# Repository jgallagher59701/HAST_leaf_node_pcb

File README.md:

# HAST leaf node pcb files

The first PCB used EagleCAD, but I've switched to KiCAD. Version 0.5 is the current version of the PCB in used as of Nov. 2021.

Supportted by a grant from ESIP.

Contact: jgallagher@opendap.org

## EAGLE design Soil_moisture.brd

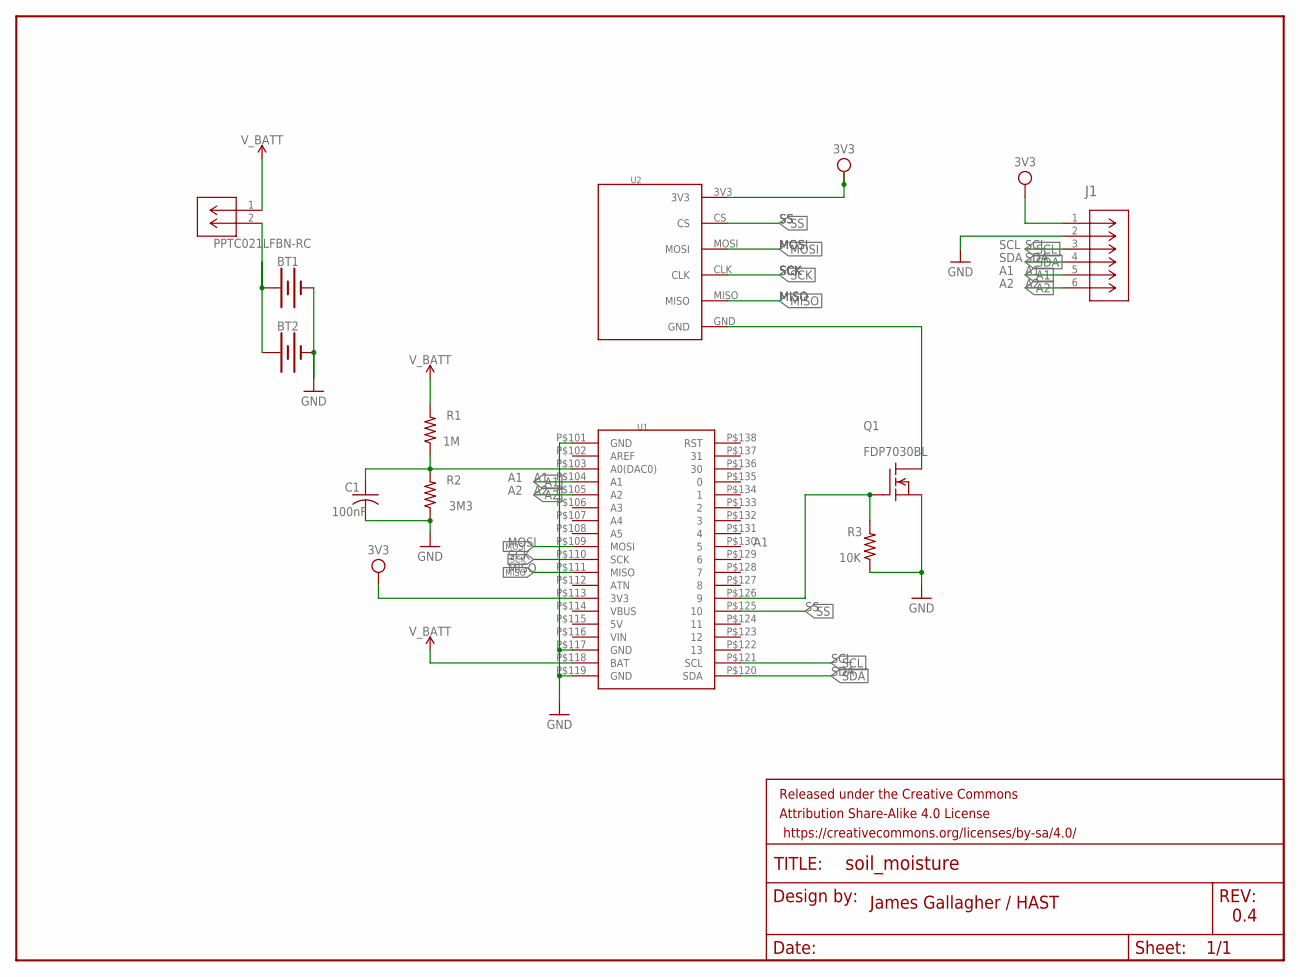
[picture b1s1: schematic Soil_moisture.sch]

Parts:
BAT_GND: PPTC021LFBN-RC; CONN2_LFBN-RC_SUL
BT1, BT2: BATTERY-AA_KIT; BATTERY-AA-KIT
C1: 100nF; C050-035X075
FRAME1: FRAME-LETTER; CREATIVE_COMMONS
J1: 1725698; CONN_1725698_PXC
Q1: FDP7030BL; TO220
R1: 1M; 0309/10
R2: 3M3; 0309/10
R3: 10K; 0309/10
U1: RS_MINI_ULTRA_PRO_V2
U2: SD_BREAKOUT_EBAY

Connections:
3V3: U1.P$113 (3V3)
A1: J1.5, U1.P$104 (A1)
A2: J1.6, U1.P$105 (A2)
GND: BT1.GND@1 (-), BT2.GND@1 (-), C1.2, J1.2, Q1.3 (S), R2.1, R3.1, U1.P$101 (GND), U1.P$117 (GND), U1.P$119 (GND)
MISO: U1.P$111 (MISO), U2.MISO
MOSI: U1.P$109 (MOSI), U2.MOSI
unnamed: Q1.2 (D), U2.GND
unnamed: C1.1, R1.1, R2.2, U1.P$103 (A0(DAC0))
unnamed: Q1.1 (G), R3.2, U1.P$126 (9)
unnamed: BAT_GND.2, BT1.PWR@1 (+), BT2.PWR@1 (+)
SCK: U1.P$110 (SCK), U2.CLK
SCL: J1.3, U1.P$121 (SCL)
SDA: J1.4, U1.P$120 (SDA)
SS: U1.P$125 (10), U2.CS
VCC: J1.1, U2.3V3
VIN: U1.P$116 (VIN)
V_BATT: BAT_GND.1, R1.2, U1.P$118 (BAT)

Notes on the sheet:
James Gallagher / HAST
0.4

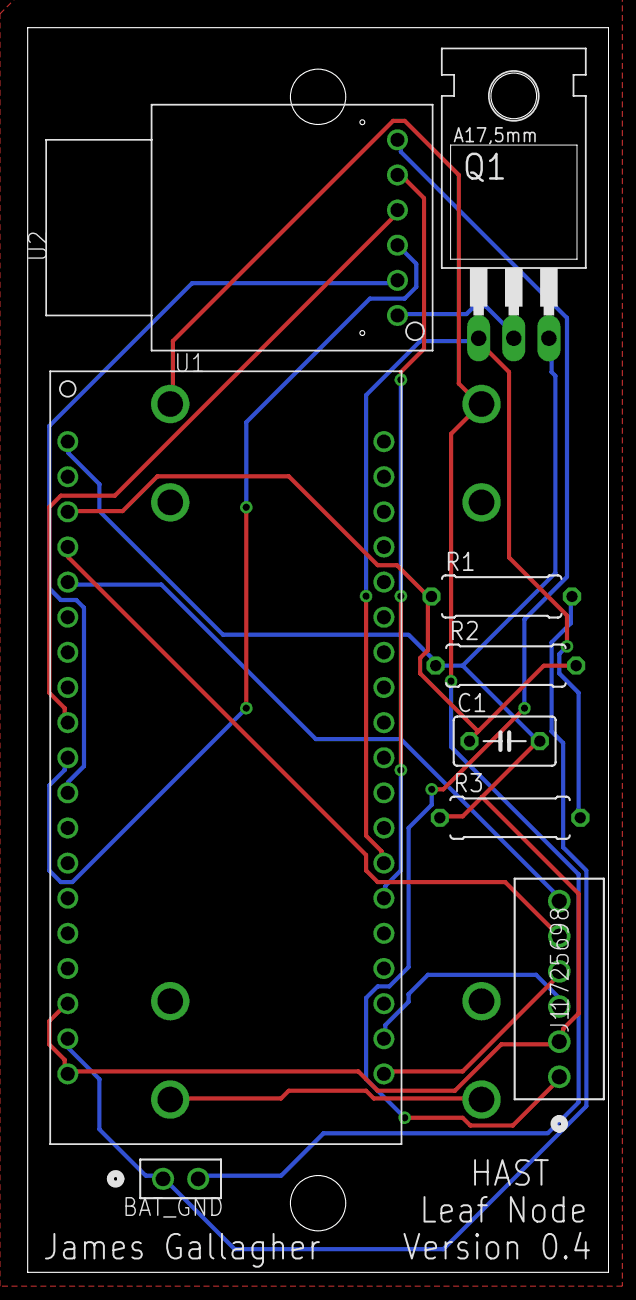
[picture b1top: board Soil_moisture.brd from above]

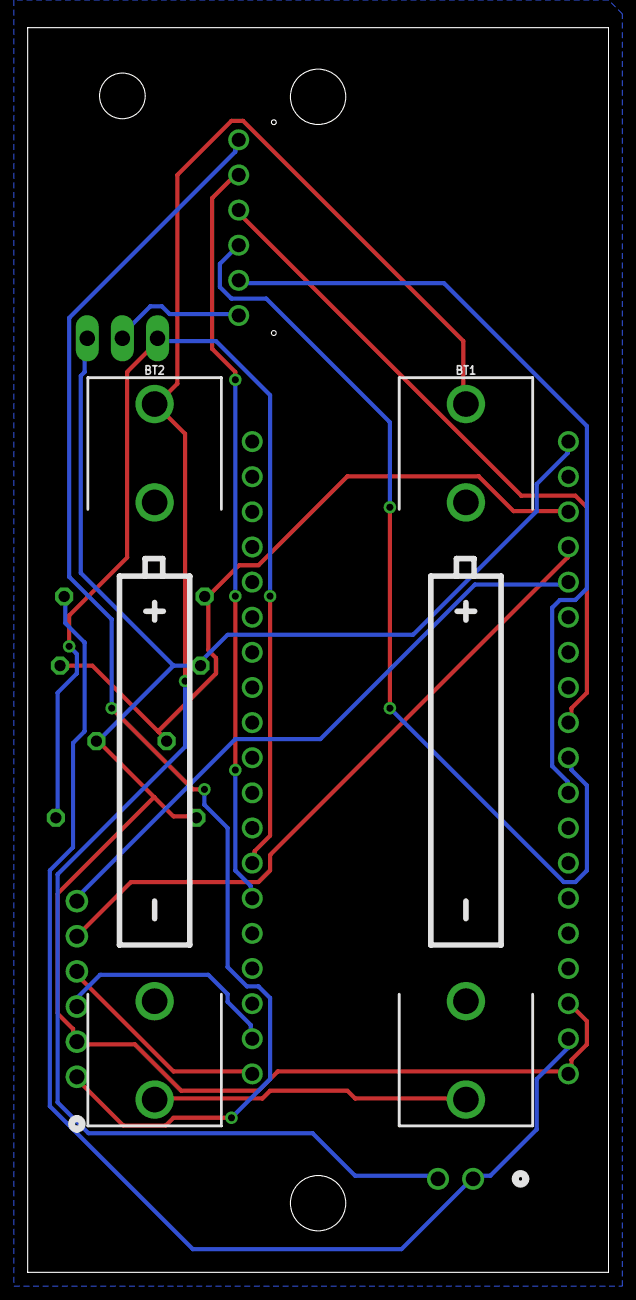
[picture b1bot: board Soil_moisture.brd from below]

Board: 2 copper layers, 42.0 x 90.0 mm, 12 parts (2 on the bottom side), 15 nets.

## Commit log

2021-03-10 Imported Eagle schematic to KiCAD, added the result here.
2021-03-10 Added a note about KiCAD 5 to the README
2021-08-27 PCB version 0.5 - now with 3D models
2021-08-28 Various hacks - added jumpers for GPIO/A0
2021-09-07 Added second voltage divider for Vbat; board outline
2021-09-09 Added Gerbers and a BOM
2021-09-13 BOM updates
2021-10-01 Added a PDF of the schematic
2021-10-01 At the office, KiCAD is using newer libraries.
    This is an update based on those newer libraries. I may
    have to update KiCAD at home to use the files on this branch.
    Test, merge if possible.
2021-11-18 Cache update
    Not sure this should be in git, but it is...

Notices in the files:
parts and their libraries:
SparkFun-Batteries: Licensing: Creative Commons ShareAlike 4.0 International - https://creativecommons.org/licenses/by-sa/4.0
SparkFun-Aesthetics: Released under the Creative Commons Attribution Share-Alike 4.0 License
SparkFun-Aesthetics: https://creativecommons.org/licenses/by-sa/4.0
